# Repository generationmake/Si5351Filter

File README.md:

# Si5351Filter
Filter board for Si 5351 for WSPR or similar purposes.

Should fit perfectly to the [Adafruit Si5351A Clock Generator Breakout Board](https://www.adafruit.com/product/2045)

## PCB

### Top

### Bottom

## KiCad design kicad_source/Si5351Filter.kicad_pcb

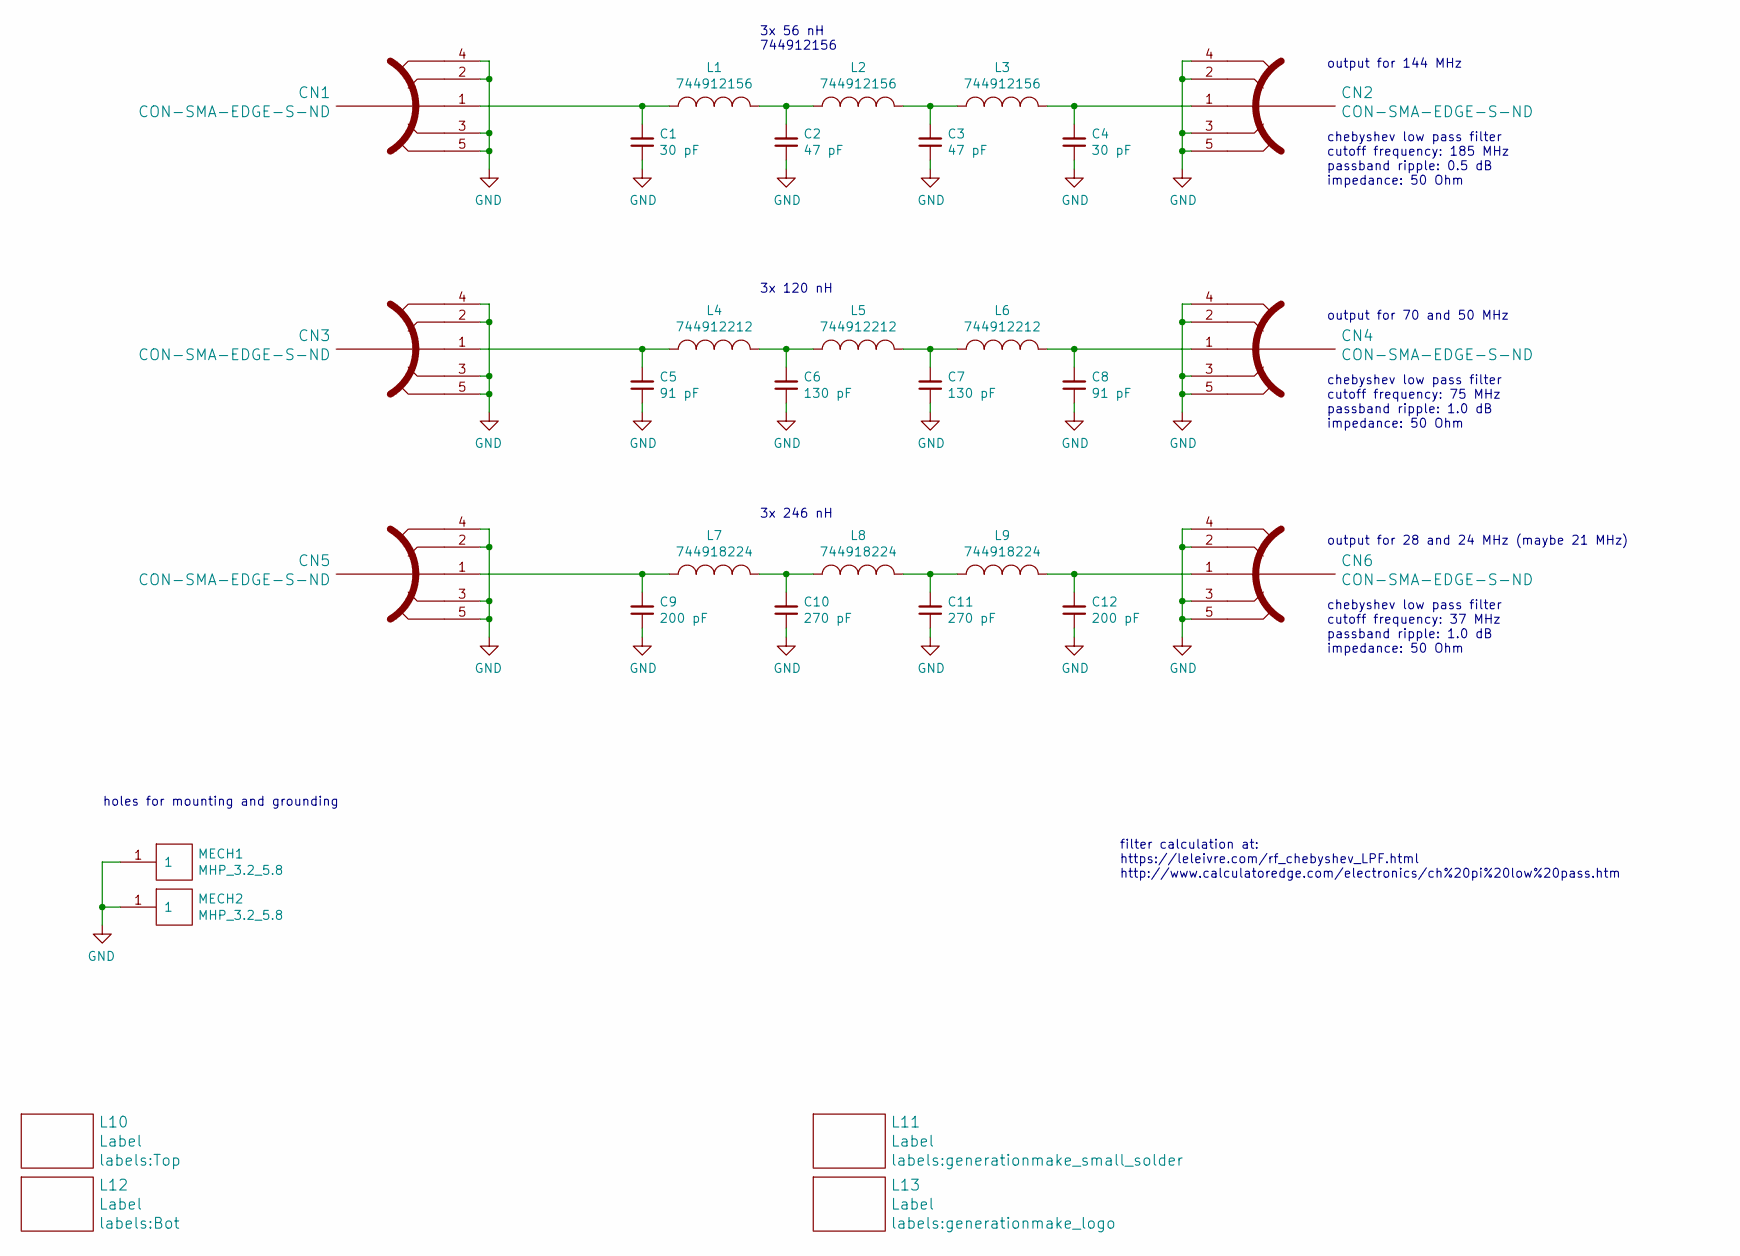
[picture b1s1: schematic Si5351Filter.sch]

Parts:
C1, C4: 30 pF; C_0603
C2, C3: 47 pF; C_0603
C5, C8: 91 pF; C_0603
C6, C7: 130 pF; C_0603
C9, C12: 200 pF; C_0603
C10, C11: 270 pF; C_0603
CN1, CN2, CN3, CN4, CN5, CN6: CON-SMA-EDGE-S-ND; WR-SMA-PCB_dual
L1, L2, L3: 744912156; WE-CAIR_4248
L4, L5, L6: 744912212; WE-CAIR_4248
L7, L8, L9: 744918224; WE-CAIR_5910
L10: Label; Top
L11: Label; generationmake_small_solder
L12: Label; Bot
L13: Label; generationmake_logo
MECH1, MECH2: MHP_3.2_5.8

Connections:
GND: C1.1, C2.1, C3.1, C4.1, C5.1, C6.1, C7.1, C8.1, C9.1, C10.1, C11.1, C12.1, CN1.2, CN1.3, CN1.4, CN1.5, CN2.2, CN2.3, CN2.4, CN2.5, CN3.2, CN3.3, CN3.4, CN3.5, CN4.2, CN4.3, CN4.4, CN4.5, CN5.2, CN5.3, CN5.4, CN5.5, CN6.2, CN6.3, CN6.4, CN6.5, MECH1.1, MECH2.1
unnamed: C1.2, CN1.1, L1.1
unnamed: C2.2, L1.2, L2.1
unnamed: C3.2, L2.2, L3.1
unnamed: C4.2, CN2.1, L3.2
unnamed: C5.2, CN3.1, L4.1
unnamed: C6.2, L4.2, L5.1
unnamed: C7.2, L5.2, L6.1
unnamed: C8.2, CN4.1, L6.2
unnamed: C9.2, CN5.1, L7.1
unnamed: C10.2, L7.2, L8.1
unnamed: C11.2, L8.2, L9.1
unnamed: C12.2, CN6.1, L9.2

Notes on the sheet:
output for 144 MHz
output for 70 and 50 MHz
3x 120 nH
3x 56 nH 744912156
chebyshev low pass filter cutoff frequency: 185 MHz passband ripple: 0.5 dB impedance: 50 Ohm
chebyshev low pass filter cutoff frequency: 75 MHz passband ripple: 1.0 dB impedance: 50 Ohm
filter calculation at: https://leleivre.com/rf_chebyshev_LPF.html http://www.calculatoredge.com/electronics/ch%20pi%20low%20pass.htm
output for 28 and 24 MHz (maybe 21 MHz)
3x 246 nH
chebyshev low pass filter cutoff frequency: 37 MHz passband ripple: 1.0 dB impedance: 50 Ohm
holes for mounting and grounding

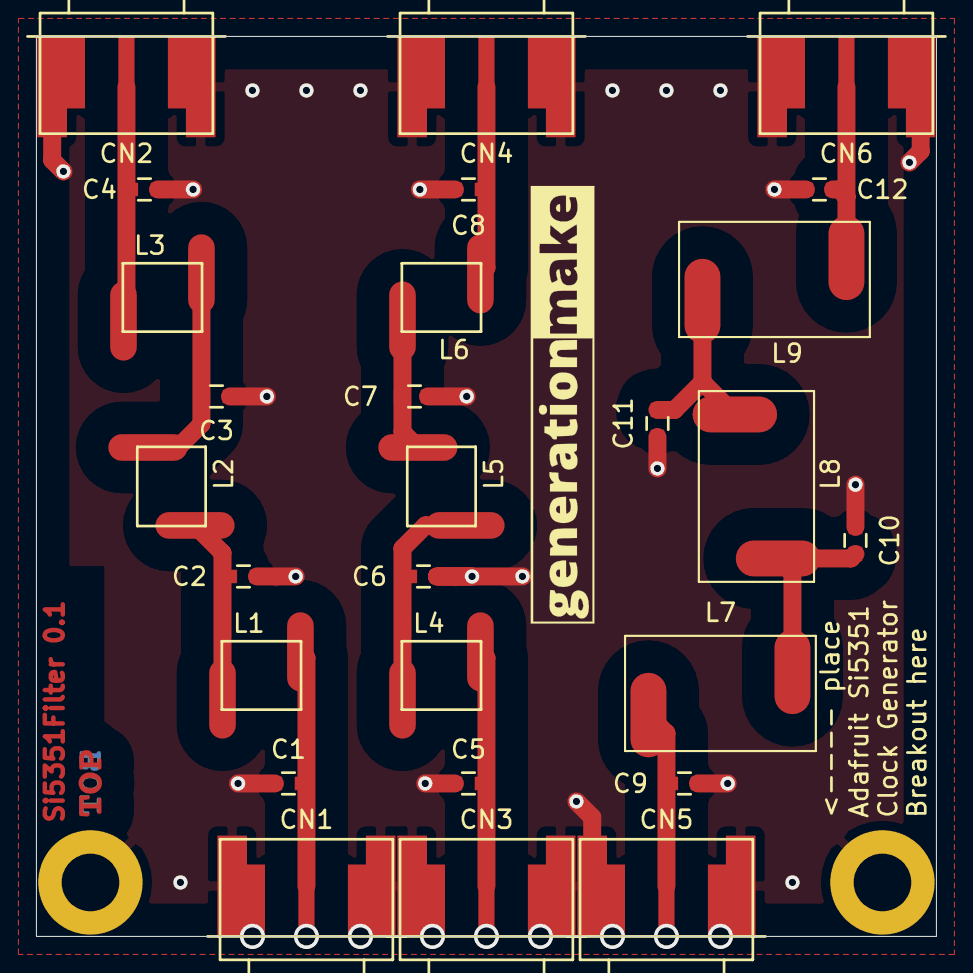
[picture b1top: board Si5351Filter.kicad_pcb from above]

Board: 2 copper layers, 50.0 x 50.0 mm, 33 parts (1 on the bottom side), 13 nets.

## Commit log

2021-08-19 added design with schematic and layout
2021-08-19 added dual footprint for big and small SMA connectors
2021-08-19 added holes for mounting and grounding
2021-08-20 updated castellated holes
2021-08-20 updated polygons
2021-09-01 added images
2021-09-01 added pdf schematic
